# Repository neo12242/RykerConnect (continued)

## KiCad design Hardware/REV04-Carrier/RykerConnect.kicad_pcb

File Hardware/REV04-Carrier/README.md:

> Historical revision: see [the hardware index](../README.md) for current options. Physical testing is pending.

# RykerConnect REV04 - socketed ESP32 carrier

**Completed prototype design, 2026-09-13.** This is the revised single-side assembly set. Use these files together; do not mix them with REV02, REV03 or the original production.zip. No boards have been ordered, assembled or physically tested.

## Files for JLCPCB

1. `manufacturing/Gerbers.zip` - two copper layers, masks, paste, silkscreen, outline and plated/non-plated drills.
2. `manufacturing/BOM.csv` - 36 components in 27 groups, every group has an explicit LCSC Part Number and manufacturer part number.
3. `manufacturing/CPL.csv` - all 36 placements are **Top**.

Start with a 102 x 46mm, two-layer FR-4, 1.6mm, 1oz copper prototype quote. The old board was 102 x 34mm. The two original mounting-hole positions remain; the enclosure needs more width and clearance above the plug-in module. Standard routing minimum clearance is 0.15mm. Do not select thicker copper without rechecking the fabrication rules.

Request top-side SMT **and through-hole assembly**. J1, J6, J7 and J8 are through-hole parts with their bodies on top; their solder joints protrude below. A single populated side does not guarantee the lowest price or eligibility for an economy SMT-only service. Check JLCPCB's process acceptance and final placement preview before paying. This task did not upload the design or obtain a quote.

The catalog stock observation on September 13 covered all 27 identities and enough available quantity for five boards. It is recorded in `validation/stock-check.json`; stock is not reserved. The socket was the smallest supply pool (52 pieces, two per board). The RTC and inductor are significant cost items; the stocked RTC is approximately $9.22 at the public single-piece tier. A final total price cannot be inferred from component prices alone.

## What changed

| Earlier shortage | REV04 treatment |
|---|---|
| C5/C9, TDK C2168289 | C5: Samsung 10uF/25V C96446; C9: larger 1206 10uF/50V C13585 |
| C6/C10, KEMET C1882722 | Samsung 100nF/50V C1591; standardized other 100nF positions too |
| D1, Toshiba C5609371 | Removed with old USB/vehicle diode OR-ing; J8 isolates the new 5V supply during USB service |
| R1-R4, KOA C5890991 | USB resistors R1/R2 removed; R3/R4 are stocked 4.7k I2C pullups C23162 |
| S1/S2, Wurth C7464054 | Carrier buttons removed; use the development board's buttons |
| U3, DS3231MZ/V+T C3304429 | DS3231SN#T&R C9866, with a new 16-pin SOIC footprint and corrected pin mapping |

The old JLCPCB spreadsheet also lacked most REV03 protection groups. The new BOM includes the entire carrier, including the retained accessory protection. U5 is now a fixed 5V AP63205WU-7 (C2071056), with its matching inductor, input/output capacitors and bootstrap circuit. The development board supplies the carrier peripherals with 3.3V. C12/C13 provide 44uF nominal at 5V. R9 moved to a stocked 0603 10k part without changing the divider ratio.

## Purchase the matching plug-in module

The socket geometry is for **Waveshare ESP32-S3-DEV-KIT-N16R8-M, SKU 28836**, the pre-soldered-header variant: 16MB flash and 8MB octal PSRAM. This documented module was selected because the exact Amazon listing's dimensions and pin mapping were not established. Do not assume another board labeled N16R8 is interchangeable.

Manufacturer references: [module overview and variants](https://docs.waveshare.com/ESP32-S3-DEV-KIT-N8R8), [drawings and schematic](https://docs.waveshare.com/ESP32-S3-DEV-KIT-N8R8/Resources-And-Documents). Source drawings are included under `sources`.

Both rows have 22 pins at 2.54mm pitch, 22.86mm apart. Module body: 63.30 x 25.40mm. The carrier drawing shows its projected outline. With the carrier text upright, the module USB connector points **left**, and its antenna points **right**. P1 plugs into J6 (upper row); P2 plugs into J7 (lower row). Pin 1 is at the antenna end of both rows. Do not shift either row by one position.

Four 2mm non-plated holes H3-H6 match the module drawing: 59.70 x 21.80mm spacing, 1.80mm from its edges. Use insulated supports and hardware appropriate to those holes; the manufacturer schematic notes M1.4 screws. Measure the fully seated module-to-carrier gap before choosing support lengths. The 8.5mm socket body plus the module header insulator makes the stack appreciably taller than a bare ESP32 module. Supports must not lift the pins out of their sockets or touch components. Keep the antenna area clear of metal, cables and a metal enclosure. RF range and vibration retention need testing with the finished assembly.

JLCPCB assembles the carrier sockets. You plug in and secure the separately purchased module afterward. That step is solderless if the specified pre-soldered module is used. The separate module, CR2032 cell, J8 shunt, remote sensor, OLED, cables, supports and enclosure are not included in the PCB BOM.

## Power and USB service

Normal operation: fused, switched accessory 12V -> protected input -> 5V buck -> **closed J8 shunt** -> development board -> 3.3V peripherals. Keep J8 closed only when USB is disconnected.

**Before connecting USB: turn off/disconnect accessory power and remove the J8 shunt.** Ignition off alone is insufficient: USB could backfeed the converter through a closed J8. After service, disconnect USB before reinstalling J8. Use a removable 2.54mm two-contact shunt; do not permanently solder J8 closed. A shunt is a separate accessory, not a missing PCB component.

J1 pin 1 is accessory +12V; pin 2 is GND. Never feed 12V into J8, the ESP headers, or J5. The buck feedback remains connected before J8, so removing the service link does not open the regulator's feedback loop. No carrier USB connector or carrier BOOT/RESET buttons remain.

The retained TPS26600 protection has nominal 17.85V overvoltage cutoff, 5.95V undervoltage startup and approximately 1A input current limiting. Its RTN and exposed pad are intentionally separate from GND. The asymmetric TVS pair has common anodes. A properly fused vehicle branch is still required. This is a prototype for normal 9-16V operation; it has no full unsuppressed load-dump or automotive certification claim. See `POWER-AND-TEST.md` for calculations and acceptance tests.

## Remote sensor and connectors

Keep the separate [Adafruit BME280 STEMMA QT module, product 2652](https://www.adafruit.com/product/2652), at about one foot / 30cm of cable. It measures temperature, relative humidity and absolute air pressure; a BMP280 cannot substitute for humidity measurement. Firmware uses 100kHz I2C. No extender is required in the initial design, but cable/noise operation must be measured.

| J5 pin | Signal |
|---|---|
| 1 | GND |
| 2 | 3.3V |
| 3 | SDA / ESP GPIO8 |
| 4 | SCL / ESP GPIO18 |

Use a correctly pinned JST SH/STEMMA QT cable and disconnect power before plugging it in. Keep the sensor away from electronics/engine heat and sun, ventilated and splash protected. Account for the breakout's parallel pullups when checking I2C edges. Board-local MCP9808 temperature remains separate from the remote BME280 reading. RTC address is 0x68; BME280 may be 0x76 or 0x77; the local MCP9808 is 0x18.

J3 OLED: pins 1 GND, 2 3.3V, 3 clock/GPIO12, 4 MOSI/GPIO11, 5 display reset/GPIO15, 6 DC/GPIO13, 7 CS1/GPIO14, 8 CS2/GPIO10. J4 light sensor: pin 1 3.3V, pin 2 GPIO7 with a 10k pull-down. Connector pin numbers, not cable colors, control wiring.

## Validation and remaining acceptance

KiCad 10.0.6 reports **zero ERC, zero DRC violations, zero unconnected items and zero schematic parity issues**. All listed DRC rule severities are enabled; no per-item exclusions are present. Silkscreen clearance and library-footprint checks were enabled and corrected, including the inherited U2 reference on the paste layer. Schematic PDFs and top/bottom board drawings were visually reviewed.

Independent net assertions check power isolation, RTC pins, display/ESP mapping, remote I2C, TVS polarity and the separate RTN network. BOM and CPL cover the same 36 references. Socket/header placement coordinates use their geometric centers, not pin 1. J1 retains its reviewed centroid adjustment; U2 retains its catalog rotation adjustment. Other rotations are native KiCad starting values. **Final JLCPCB model alignment and process acceptance remain unverified**, especially connector pin 1, diode cathodes, U3/U5/U6 orientation and the long sockets.

The N16R8 firmware target built successfully. Hardware boot, flash/PSRAM detection, electrical load/temperature, enclosure fit, vibration and vehicle transients cannot be validated without an assembled prototype. Follow `POWER-AND-TEST.md` before vehicle installation. REV03 hardware and original Downloads inputs match their prior hashes. REV04 firmware copies the current workspace REV02 source, which already differs from the older REV03 delivery; this task adds the N16R8 configuration in a separate folder and does not edit the prior firmware.

## Firmware and rebuilding

Use `Firmware/RykerConnect-REV04` in the delivery archive and the `RykerConnect_REV04` PlatformIO environment. See its `REV04-README.md`. The source preserves existing display, RTC and remote-sensor behavior; this revision changes the flash/PSRAM configuration. The Android application was not changed or rebuilt in this task.

Open `RykerConnect.kicad_pro` to edit. The local symbol and footprint libraries are included. Generation scripts require KiCad 10's bundled Python; `export_release.py`, `check_calculations.py`, and `render_previews.py` use ordinary Python. `rebuild.py` reproduces the reviewed routes from `validation/carrier.ses`; no autorouter download is needed. Its small preserved REV03 input set is included alongside REV04 in the archive. Intentional rerouting invalidates the final manual routing adjustments and requires another complete review.

Original RykerConnect attribution and license are retained in the delivery archive. No original manufacturer source document was treated as an instruction to take action.

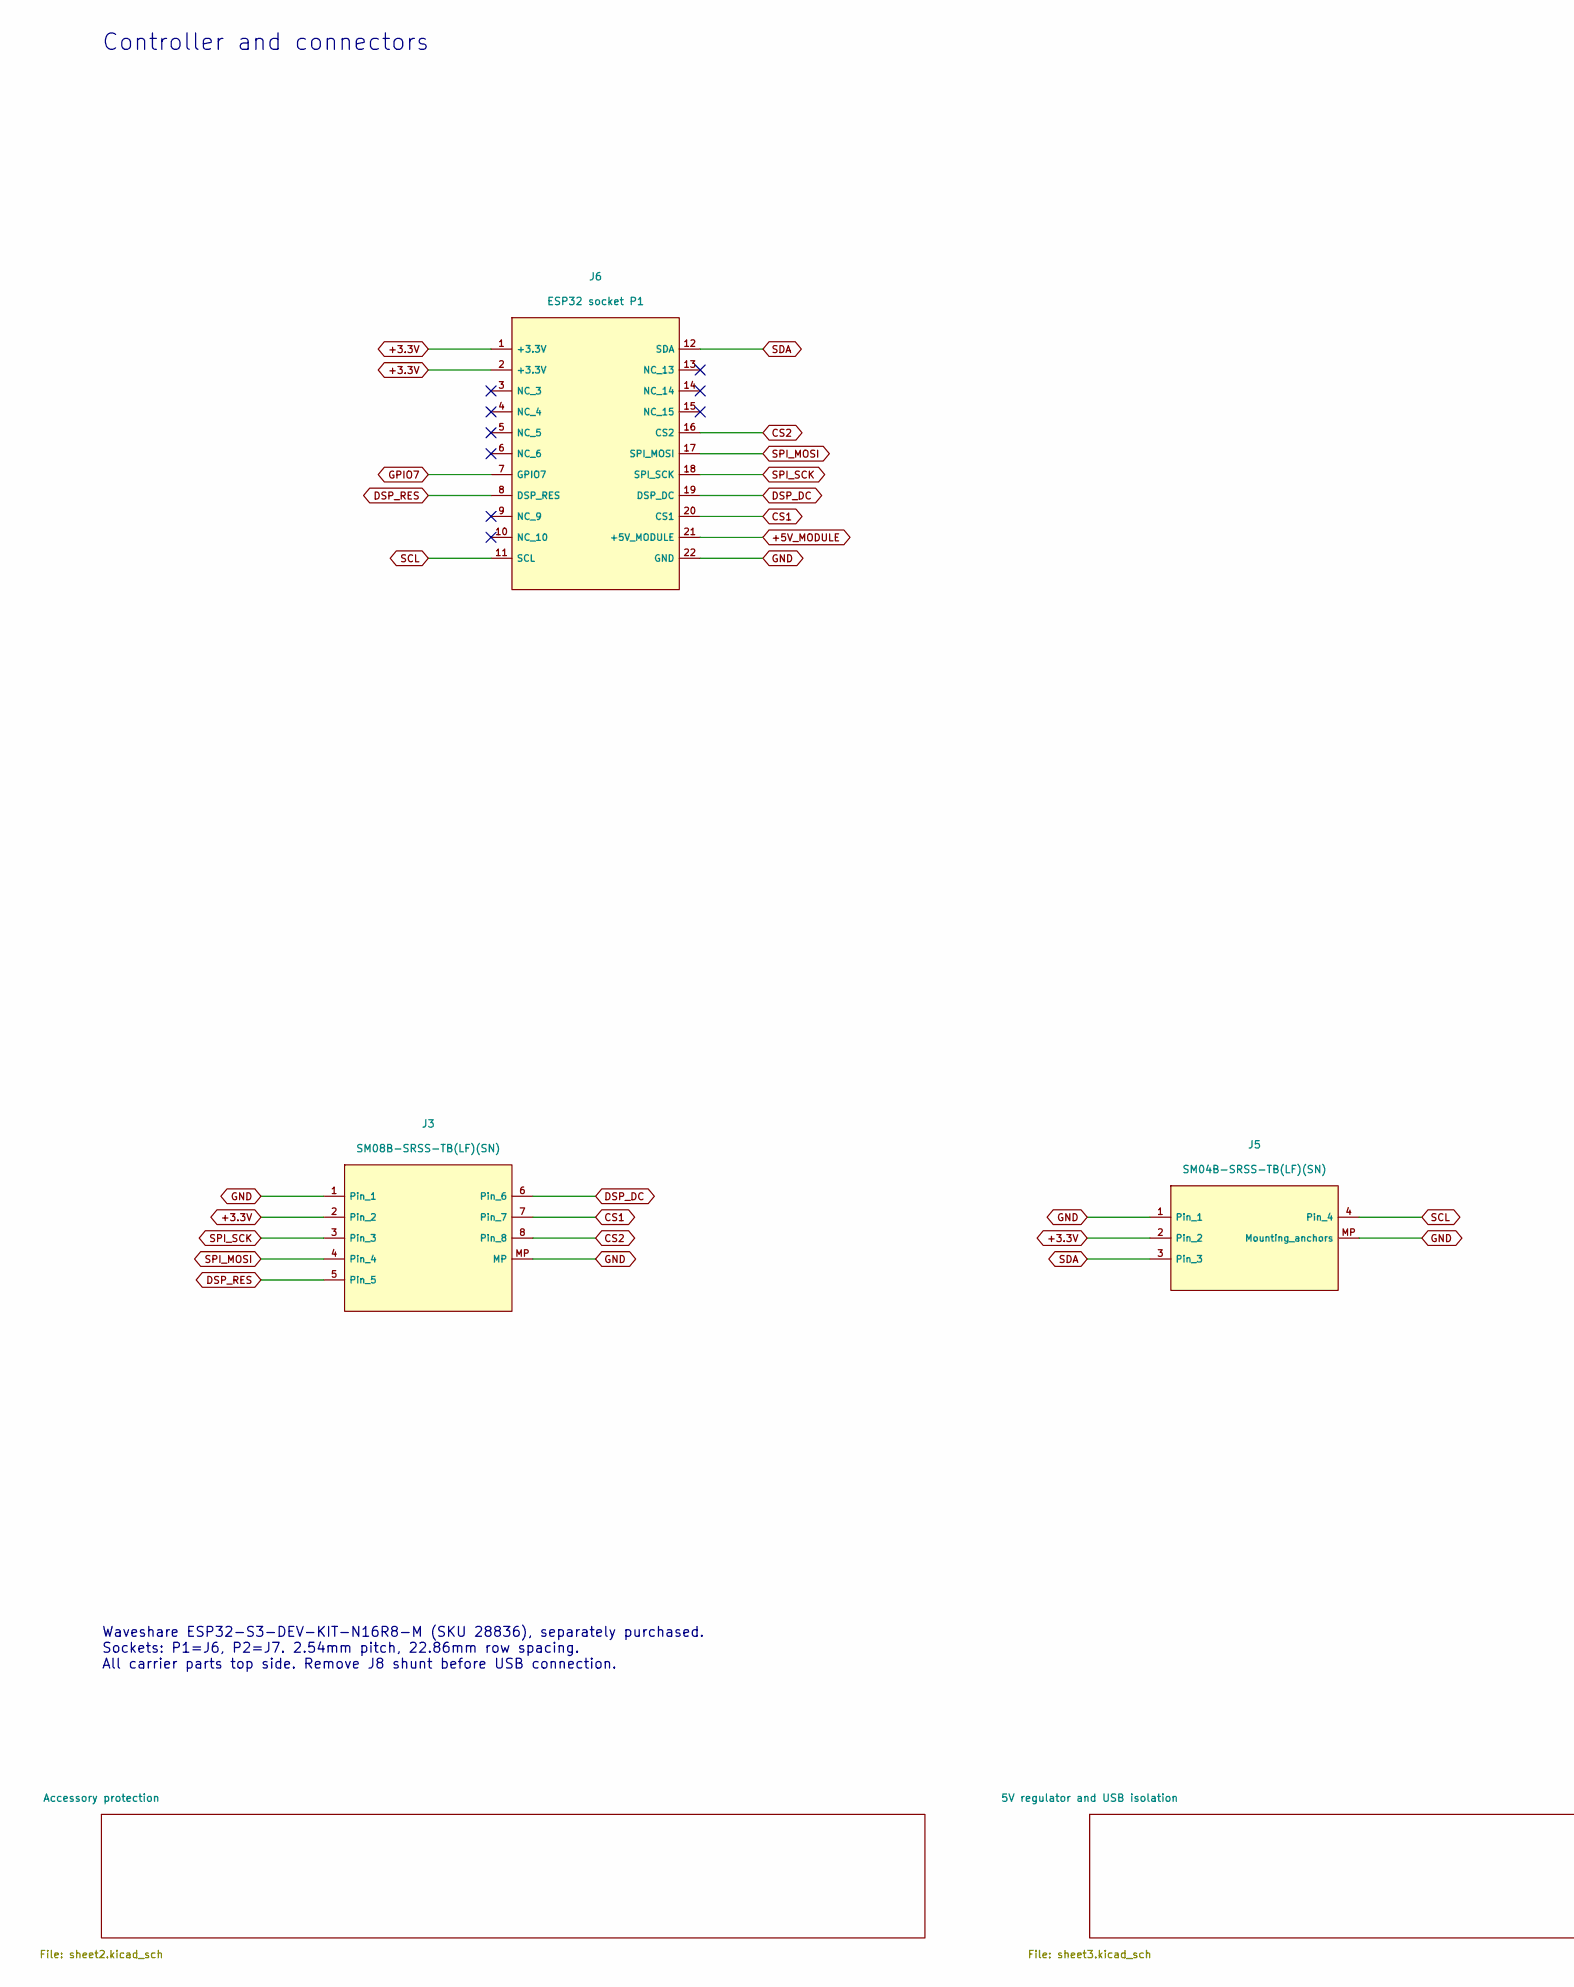
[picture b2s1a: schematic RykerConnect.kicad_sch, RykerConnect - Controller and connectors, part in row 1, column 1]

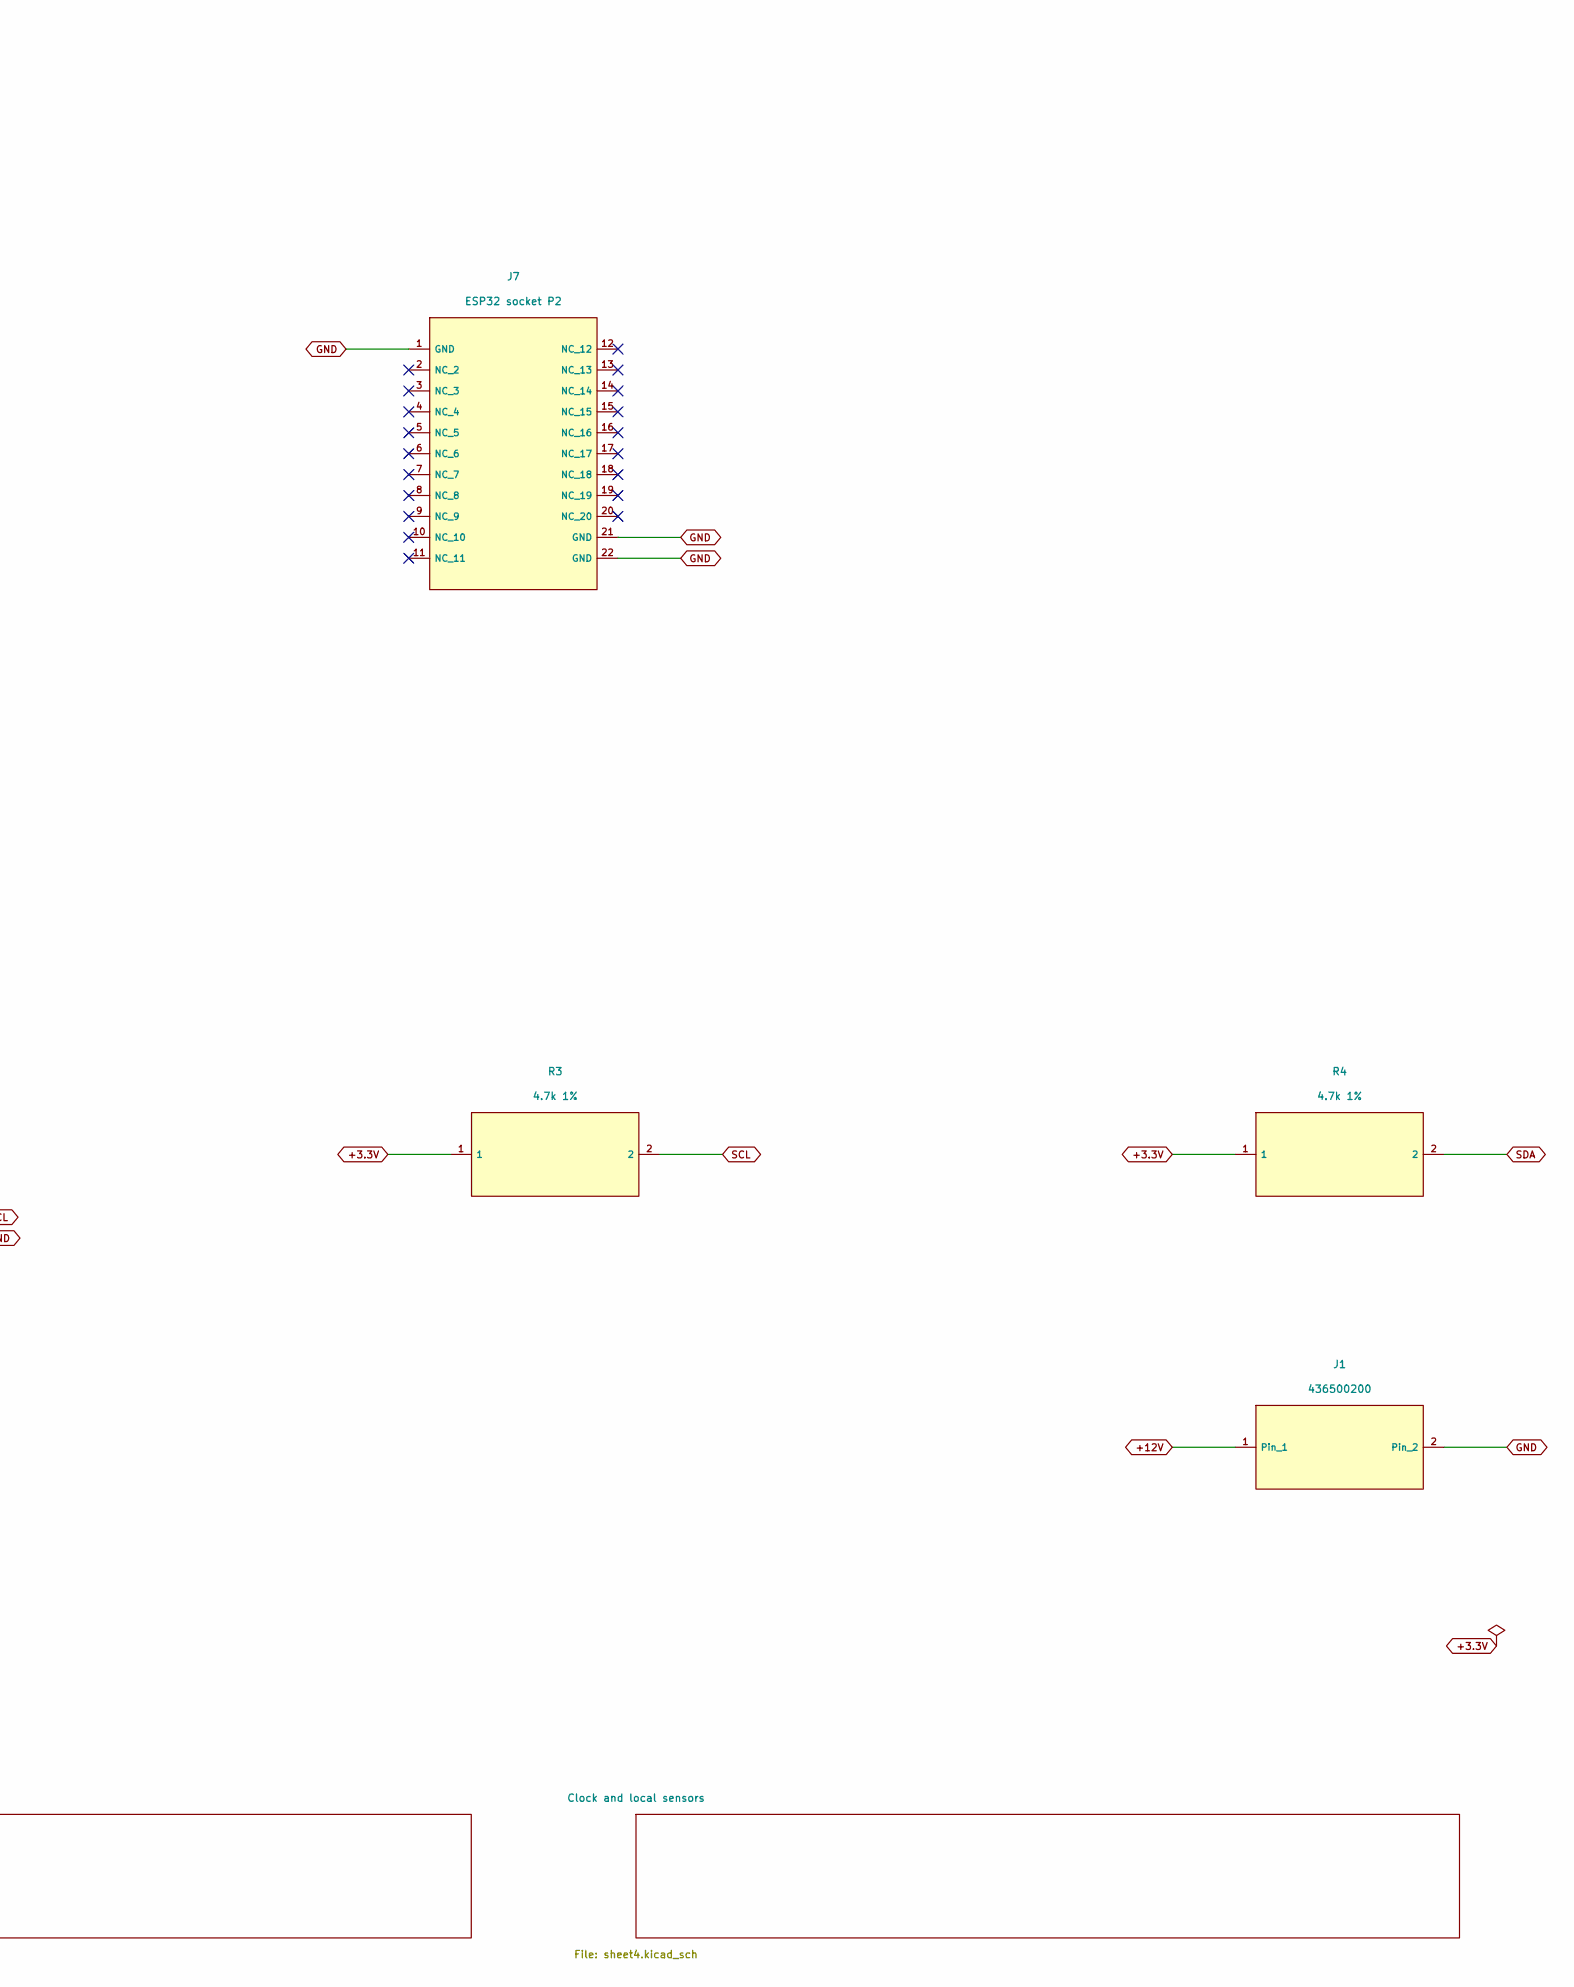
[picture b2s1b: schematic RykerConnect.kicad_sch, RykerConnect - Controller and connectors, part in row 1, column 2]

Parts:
J1: 436500200; J1_J1_43650-02_00,01,02_; MPN 436500200; LCSC C192562
J3: SM08B-SRSS-TB(LF)(SN); J3_J3_JST_SH_SM08B-SRSS-TB_1x08-1MP_P1.00mm_Horizontal; MPN SM08B-SRSS-TB(LF)(SN); LCSC C160407
J5: SM04B-SRSS-TB(LF)(SN); J5_J5_JST_SH_SM04B-SRSS-TB_1x04-1MP_P1.00mm_Horizontal; MPN SM04B-SRSS-TB(LF)(SN); LCSC C160404
J6: ESP32 socket P1; J6_PinSocket_1x22_P2.54mm_Vertical; MPN FH2.54-09-22PZD; LCSC C7500786
J7: ESP32 socket P2; J7_PinSocket_1x22_P2.54mm_Vertical; MPN FH2.54-09-22PZD; LCSC C7500786
R3: 4.7k 1%; R3_R_0603_1608Metric; MPN 0603WAF4701T5E; LCSC C23162
R4: 4.7k 1%; R4_R_0603_1608Metric; MPN 0603WAF4701T5E; LCSC C23162

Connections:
+3.3V: J3.2, J5.2, J6.1 (+3.3V), J6.2 (+3.3V), R3.1, R4.1; also elsewhere on the board
+5V_MODULE: J6.21 (+5V_MODULE); also elsewhere on the board
+12V: J1.1; also elsewhere on the board
CS1: J3.7, J6.20 (CS1)
CS2: J3.8, J6.16 (CS2)
DSP_DC: J3.6, J6.19 (DSP_DC)
DSP_RES: J3.5, J6.8 (DSP_RES)
GND: J1.2, J3.1, J3.MP, J5.1, J5.MP (Mounting_anchors), J6.22 (GND), J7.1 (GND), J7.21 (GND), J7.22 (GND); also elsewhere on the board
GPIO7: J6.7 (GPIO7); also elsewhere on the board
SCL: J5.4, J6.11 (SCL), R3.2; also elsewhere on the board
SDA: J5.3, J6.12 (SDA), R4.2; also elsewhere on the board
SPI_MOSI: J3.4, J6.17 (SPI_MOSI)
SPI_SCK: J3.3, J6.18 (SPI_SCK)

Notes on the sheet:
Controller and connectors
Waveshare ESP32-S3-DEV-KIT-N16R8-M (SKU 28836), separately purchased. Sockets: P1=J6, P2=J7. 2.54mm pitch, 22.86mm row spacing. All carrier parts top side. Remove J8 shunt before USB connection.

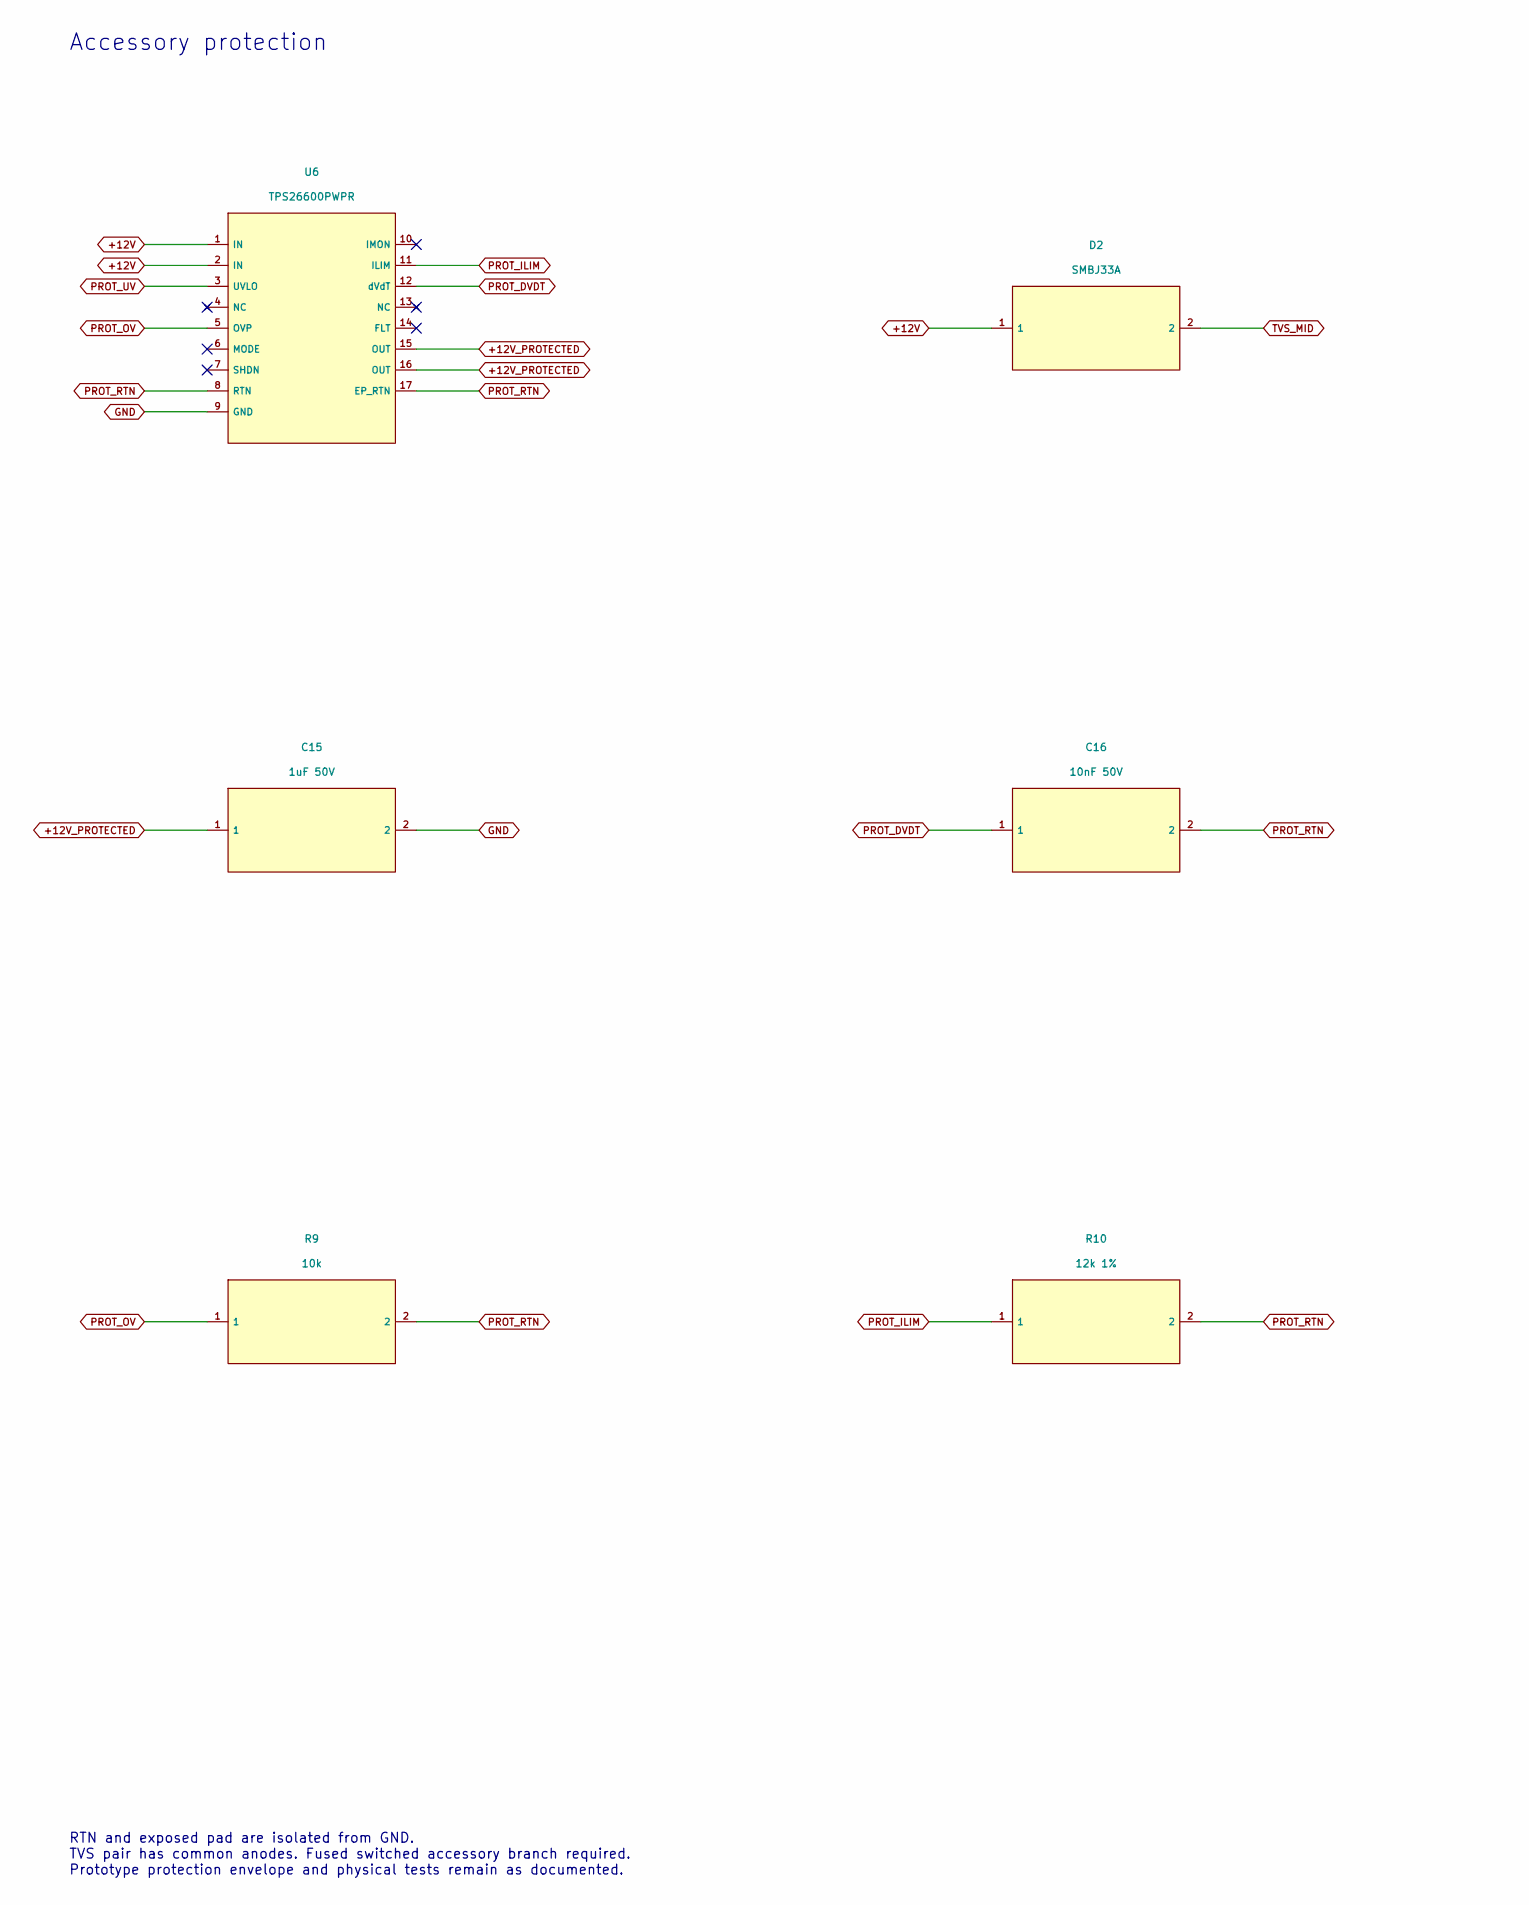
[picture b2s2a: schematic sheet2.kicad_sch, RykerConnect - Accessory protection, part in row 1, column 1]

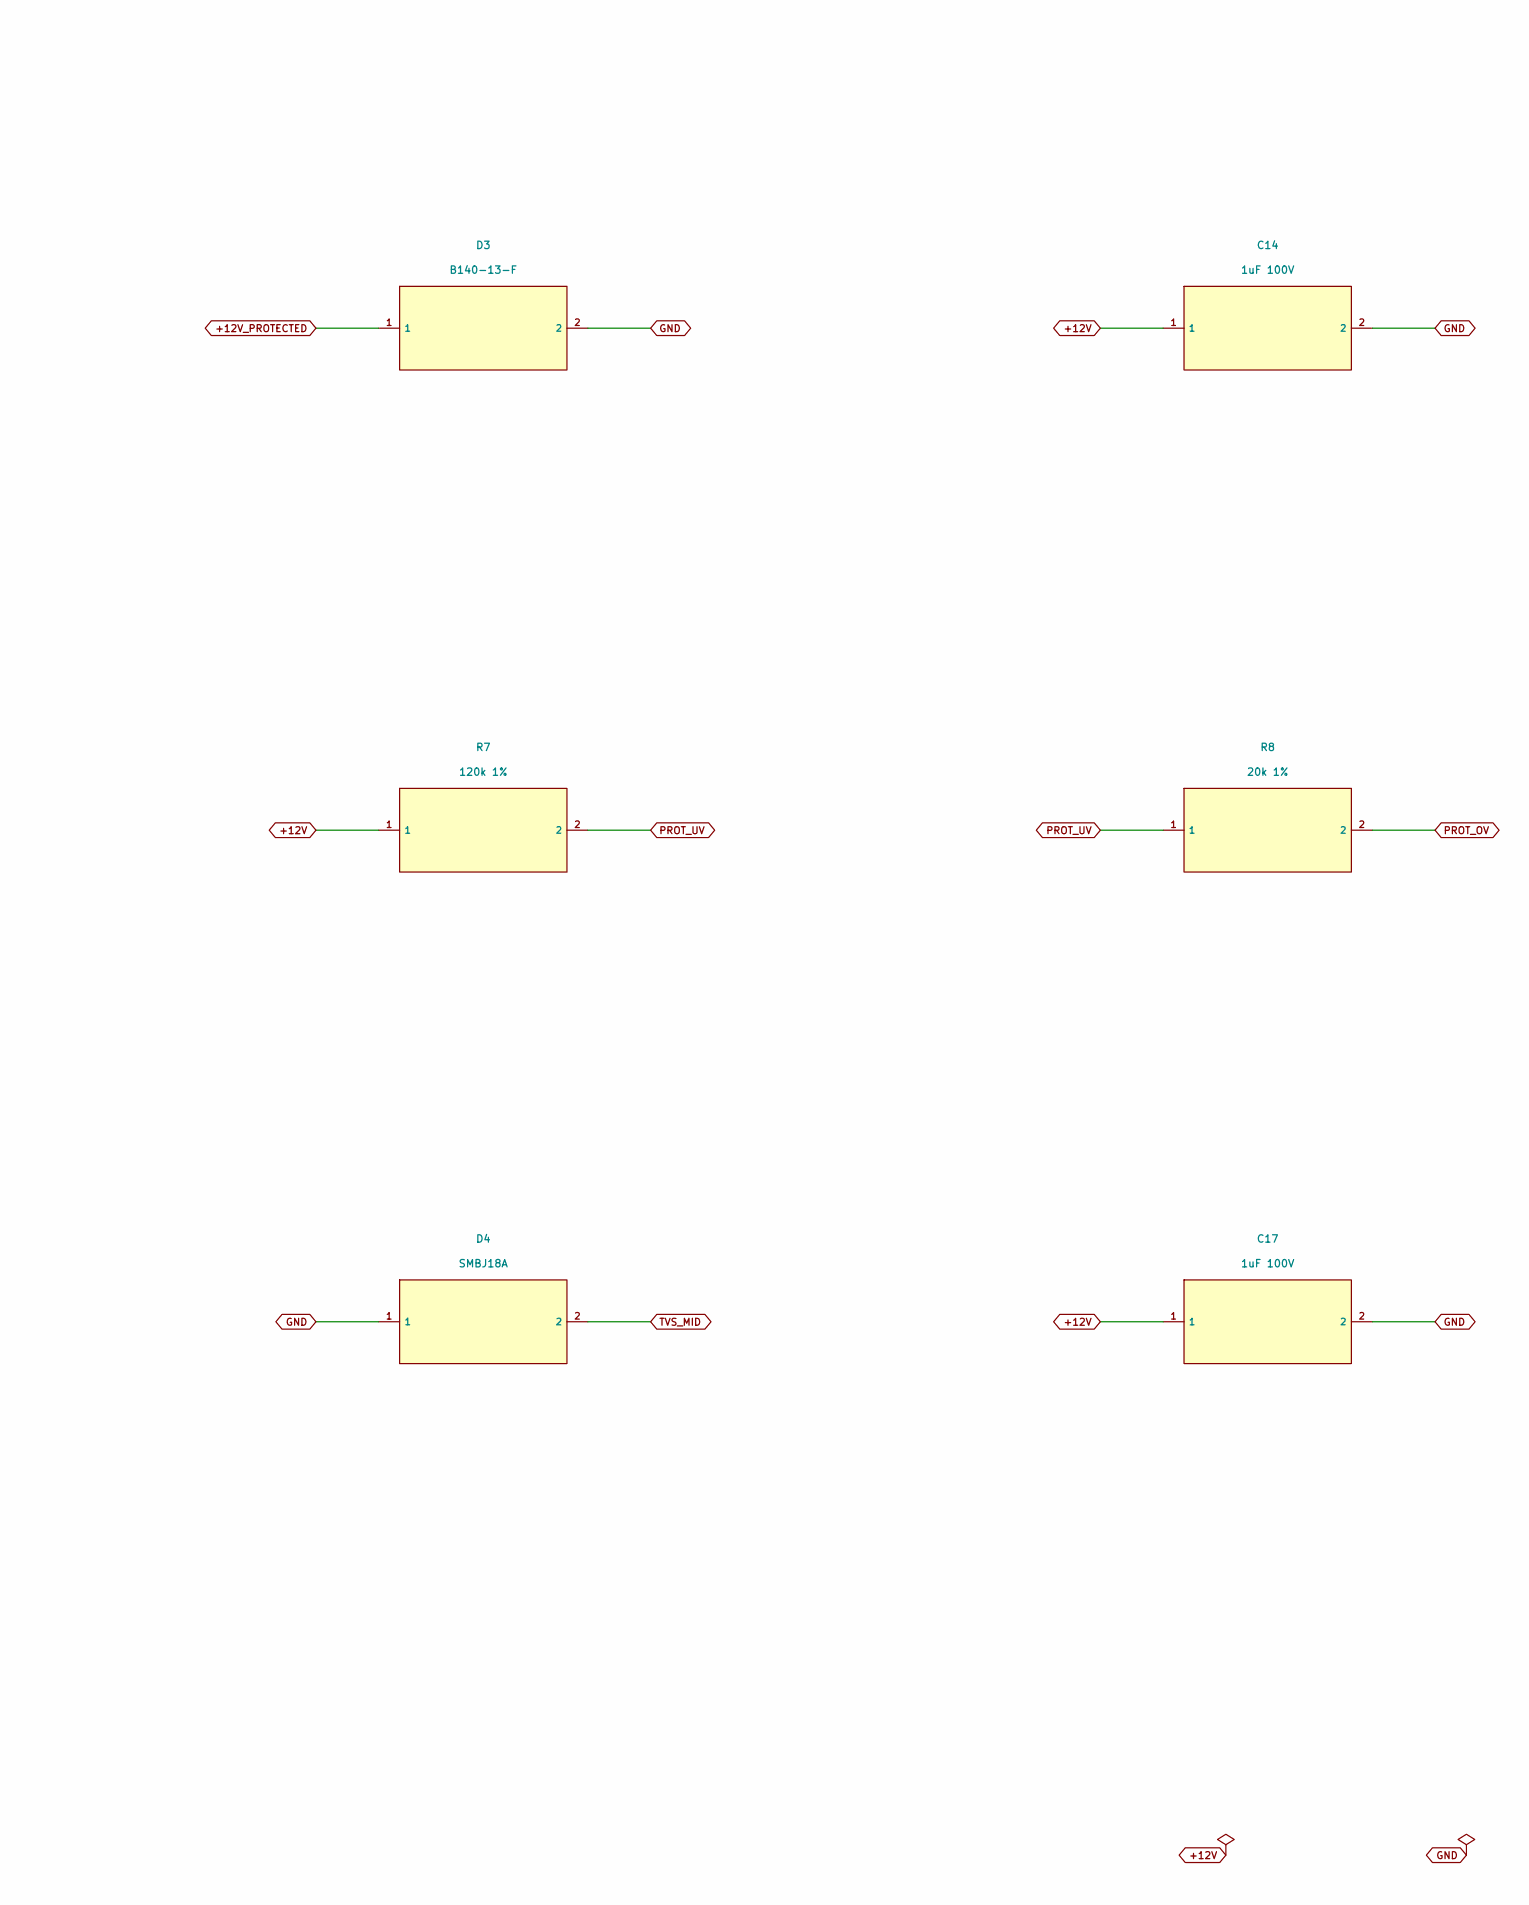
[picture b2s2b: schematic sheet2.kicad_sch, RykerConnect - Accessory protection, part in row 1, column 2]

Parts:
C14: 1uF 100V; C14_C_1206_3216Metric; MPN CL31B105KCHNNNE; LCSC C13832
C15: 1uF 50V; C15_C_0805_2012Metric; MPN CL21B105KBFNNNE; LCSC C28323
C16: 10nF 50V; C16_C_0603_1608Metric; MPN CL10B103KB8NNNC; LCSC C1589
C17: 1uF 100V; C17_C_1206_3216Metric; MPN CL31B105KCHNNNE; LCSC C13832
D2: SMBJ33A; D2_D_SMB; MPN SMBJ33A; LCSC C224019
D3: B140-13-F; D3_D_SMA; MPN B140-13-F; LCSC C15759
D4: SMBJ18A; D4_D_SMB; MPN SMBJ18A; LCSC C151256
R7: 120k 1%; R7_R_0603_1608Metric; MPN RC0603FR-07120KL; LCSC C114607
R8: 20k 1%; R8_R_0603_1608Metric; MPN RC0603FR-0720KL; LCSC C105575
R9: 10k; R9_R_0603_1608Metric; MPN 0603WAF1002T5E; LCSC C25804
R10: 12k 1%; R10_R_0603_1608Metric; MPN RC0603FR-0712KL; LCSC C114659
U6: TPS26600PWPR; U6_U6_Protection_HTSSOP16_PWP0016A; MPN TPS26600PWPR; LCSC C544399

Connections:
+12V: C14.1, C17.1, D2.1, R7.1, U6.1 (IN), U6.2 (IN); also elsewhere on the board
+12V_PROTECTED: C15.1, D3.1, U6.15 (OUT), U6.16 (OUT); also elsewhere on the board
GND: C14.2, C15.2, C17.2, D3.2, D4.1, U6.9 (GND); also elsewhere on the board
PROT_DVDT: C16.1, U6.12 (dVdT)
PROT_ILIM: R10.1, U6.11 (ILIM)
PROT_OV: R8.2, R9.1, U6.5 (OVP)
PROT_RTN: C16.2, R9.2, R10.2, U6.8 (RTN), U6.17 (EP_RTN)
PROT_UV: R7.2, R8.1, U6.3 (UVLO)
TVS_MID: D2.2, D4.2

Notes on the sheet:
Accessory protection
RTN and exposed pad are isolated from GND. TVS pair has common anodes. Fused switched accessory branch required. Prototype protection envelope and physical tests remain as documented.
